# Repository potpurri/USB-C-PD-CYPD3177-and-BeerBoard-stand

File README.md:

# USB Power Delivery Board (CYPD-3177) / BeerBoard-stand

**THIS IS AN OLD DESIGN, FOR VER 2 LOOK AT [THIS REPOSITORY](https://github.com/potpurri/USB-C_PD_Board_V2_CYPD3177).**

This **USB Power Delivery (PD) Board** is based around the **CYPD-3177** chipset. The board allows users to select the desired output **voltage** and **current** using onboard switches, making it ideal for powering my **breadboard projects**. [Schematic can be found here.](https://github.com/potpurri/USB-C-PD-CYPD3177-and-BeerBoard-stand/blob/f3c342192d2ab72d846928ec36ac7f8050d37a6a/imgs/Schematic.pdf)

Users can choose between the following **voltage levels**: **5V, 9V, 12V, 15V, and 20V**, and **current levels**: **1A, 2A, 3A, 4A, and 5A**, depending on the configuration and power supply capabilities.

(The underside of the board also functions as a stand for the [BeerBoard](https://github.com/potpurri/BeerBoard))

The board is soldered by me using a [Pinecil V2](https://wiki.pine64.org/wiki/Pinecil) by PINE64  and [MHP50](https://e-design.com.cn/en/Mini-Hot-Plate-Preheater-MHP50-PG9555615) by MiniWare.

## Key Features
- Based on the **CYPD-3177** USB PD controller
- User-selectable output **voltage**: **5V, 9V, 12V, 15V, and 20V**
- User-selectable output **current**: **1A, 2A, 3A, 4A, and 5A**
- Supports standard USB Power Delivery profiles for flexible power output; compact and versatile

## Images

### Assembled Images

### 3D Image

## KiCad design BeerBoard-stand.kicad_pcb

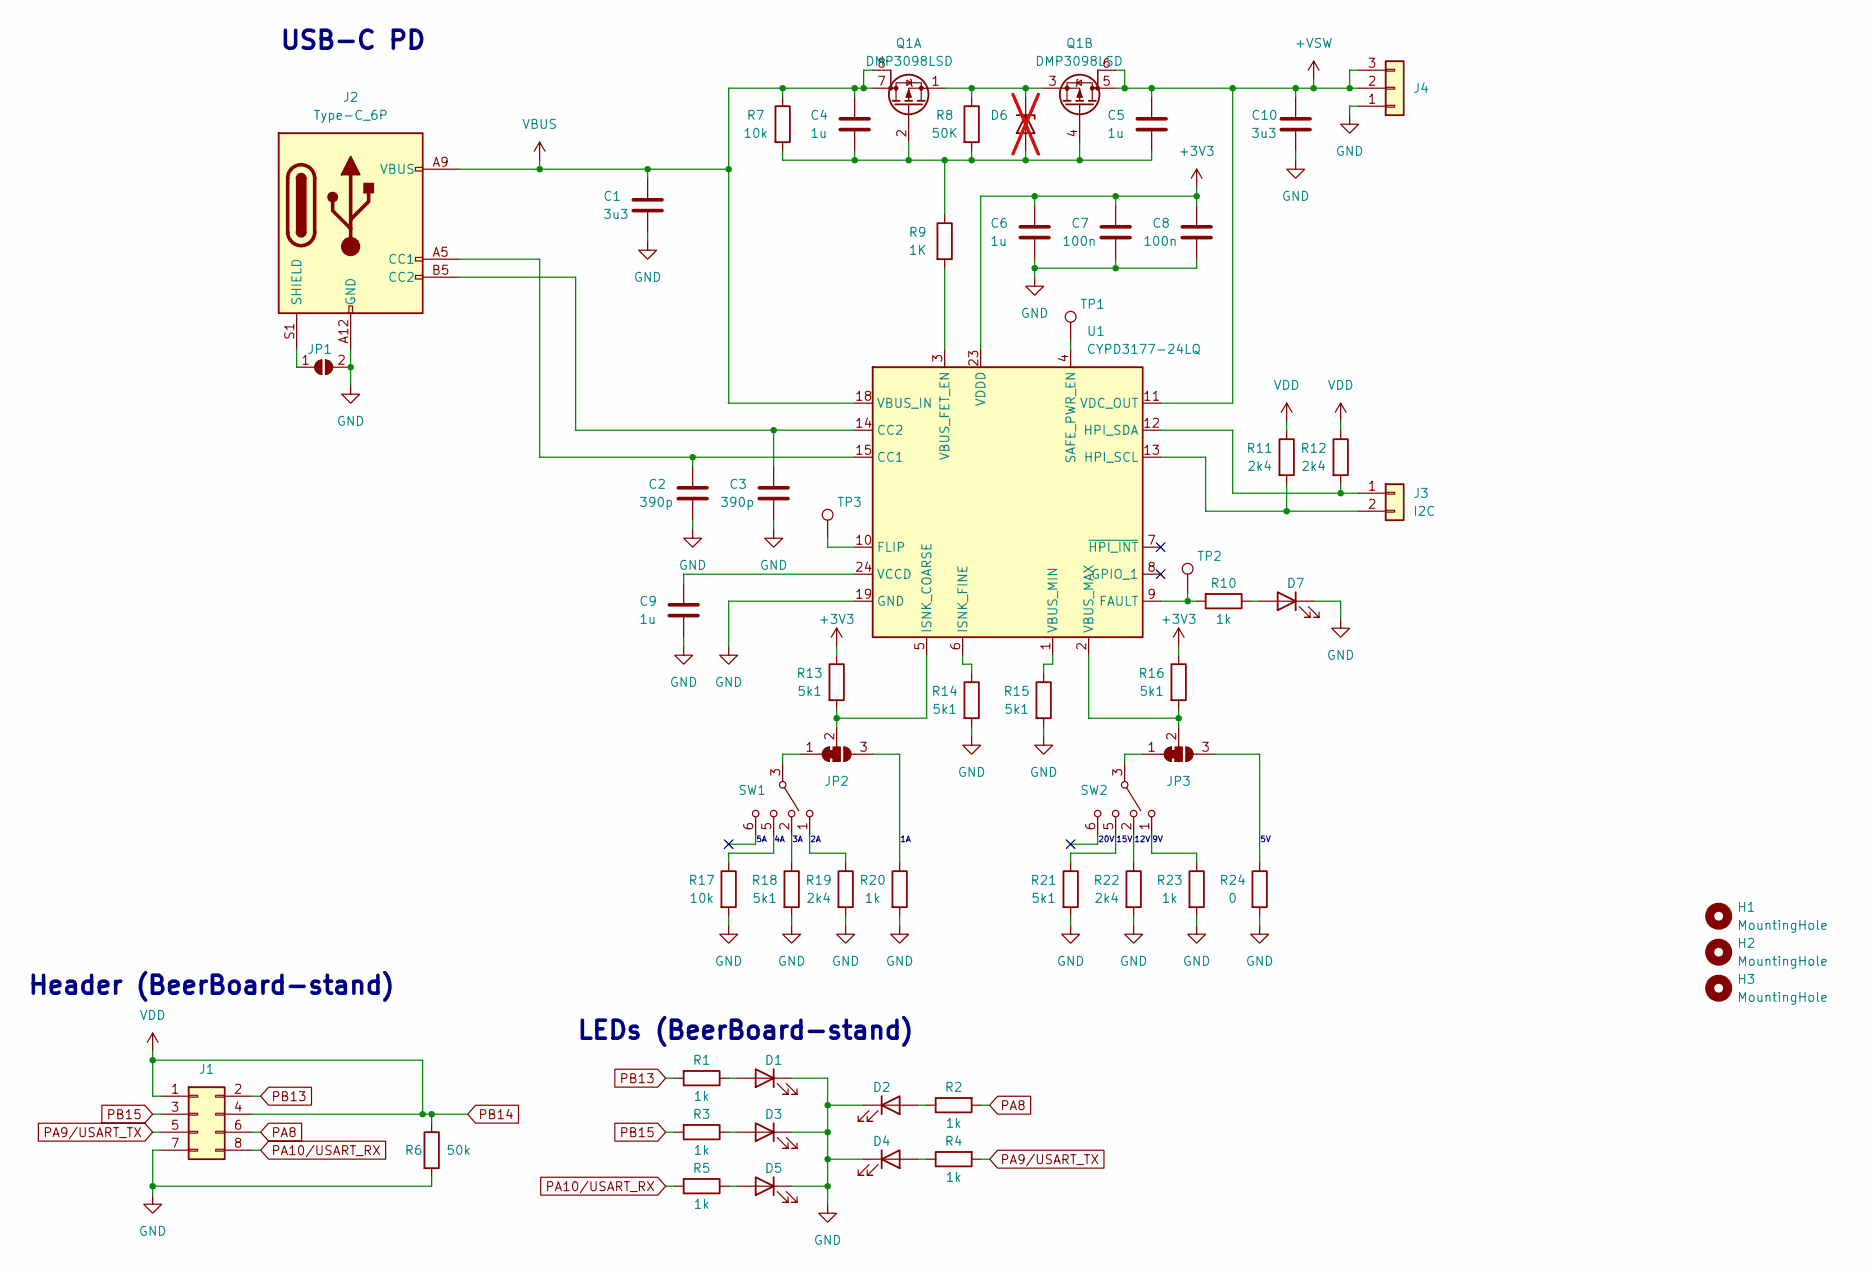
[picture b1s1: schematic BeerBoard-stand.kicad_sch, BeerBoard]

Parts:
C1, C10: 3u3; C_0805_2012Metric_Pad1.18x1.45mm_HandSolder
C2, C3: 390p; C_0603_1608Metric_Pad1.08x0.95mm_HandSolder
C4, C5, C6, C9: 1u; C_0805_2012Metric_Pad1.18x1.45mm_HandSolder
C7, C8: 100n; C_0603_1608Metric_Pad1.08x0.95mm_HandSolder
D1, D2, D3, D4, D5, D7: LED; LED_0805_2012Metric_Pad1.15x1.40mm_HandSolder
D6: D_Zener; D_DO-35_SOD27_P7.62mm_Horizontal; not fitted
H1, H2, H3: MountingHole; MountingHole_3.2mm_M3
J1: Conn_02x04_Odd_Even; PinHeader_2x04_P2.54mm_Vertical
J2: Type-C_6P; USB_C_Receptacle_GCT_USB4125-xx-x-0190_6P_TopMnt_Horizontal
J3: I2C; PinHeader_1x02_P2.54mm_Vertical
J4: Conn_01x03; PinHeader_1x03_P2.54mm_Vertical
JP1: SolderJumper_2_Open; SolderJumper-2_P1.3mm_Open_RoundedPad1.0x1.5mm
JP2, JP3: SolderJumper_3_Bridged12; SolderJumper-3_P1.3mm_Bridged2Bar12_RoundedPad1.0x1.5mm_Num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
Q1: DMP3098LSD; SOIC-8-1EP_3.9x4.9mm_P1.27mm_EP2.29x3mm
R1, R2, R3, R4, R5, R10, R20, R23: 1k; R_0603_1608Metric
R6: 50k; R_0603_1608Metric
R7, R17: 10k; R_0603_1608Metric
R8: 50K; R_0603_1608Metric
R9: 1K; R_0603_1608Metric
R11, R12, R19, R22: 2k4; R_0603_1608Metric
R13, R14, R15, R16, R18, R21: 5k1; R_0603_1608Metric
R24: 0; R_0603_1608Metric
SW1, SW2: SK-14D01-G 6
TP1, TP2, TP3: TestPoint; TestPoint_Pad_1.0x1.0mm
U1: CYPD3177-24LQ; QFN-24-1EP_4x4mm_P0.5mm_EP2.75x2.75mm

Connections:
+3V3: C6.1, C7.1, C8.1, R13.1, R16.1, U1.23 (VDDD)
+VSW: C5.1, C10.1, J4.2, J4.3, Q1.5 (D), Q1.6 (G), U1.11 (VDC_OUT)
CC1: C2.1, J2.A5 (CC1), U1.15 (CC1)
CC2: C3.1, J2.B5 (CC2), U1.14 (CC2)
GND: C1.2, C2.2, C3.2, C6.2, C7.2, C8.2, C9.2, C10.2, D1.1 (K), D2.1 (K), D3.1 (K), D4.1 (K), D5.1 (K), D7.1 (K), J1.7, J2.A12 (GND), J2.B12 (GND), J4.1, JP1.2 (B), R6.2, R14.2, R15.2, R17.2, R18.2, R19.2, R20.2, R21.2, R22.2, R23.2, R24.2, U1.19 (GND), U1.22 (GND), U1.25 (GND)
unnamed: D1.2 (A), R1.1
unnamed: D2.2 (A), R2.1
unnamed: D3.2 (A), R3.1
unnamed: D4.2 (A), R4.1
unnamed: D5.2 (A), R5.1
unnamed: C4.2, C5.2, D6.2 (A), Q1.2 (G), Q1.4 (G), R7.2, R8.2, R9.1
unnamed: D6.1 (K), Q1.1 (S), Q1.3 (S), R8.1
unnamed: D7.2 (A), R10.1
unnamed: J2.S1 (SHIELD), JP1.1 (A)
unnamed: J3.1, R12.2, U1.12 (HPI_SDA)
unnamed: J3.2, R11.2, U1.13 (HPI_SCL)
unnamed: JP2.1 (A), SW1.3, SW1.4
unnamed: JP2.3 (B), R20.1
unnamed: JP2.2 (C), R13.2, U1.5 (ISNK_COARSE)
unnamed: JP3.1 (A), SW2.3, SW2.4
unnamed: JP3.3 (B), R24.1
unnamed: JP3.2 (C), R16.2, U1.2 (VBUS_MAX)
unnamed: R17.1, SW1.5
unnamed: R18.1, SW1.2
unnamed: R19.1, SW1.1
unnamed: R21.1, SW2.5
unnamed: R22.1, SW2.2
unnamed: R23.1, SW2.1
unnamed: R10.2, TP2.1, U1.9 (FAULT)
unnamed: TP3.1, U1.10 (FLIP)
unnamed: R14.1, U1.6 (ISNK_FINE)
unnamed: TP1.1, U1.4 (SAFE_PWR_EN)
unnamed: R9.2, U1.3 (VBUS_FET_EN)
unnamed: R15.1, U1.1 (VBUS_MIN)
unnamed: C9.1, U1.24 (VCCD)
PA8: J1.6, R2.2
PA9/USART_TX: J1.5, R4.2
PA10/USART_RX: J1.8, R5.2
PB13: J1.2, R1.2
PB14: J1.1, J1.4, R6.1, R11.1, R12.1
PB15: J1.3, R3.2
VBUS: C1.1, C4.1, J2.A9 (VBUS), J2.B9 (VBUS), Q1.7 (D), Q1.8 (G), R7.1, U1.18 (VBUS_IN)

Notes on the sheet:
USB-C PD
Header (BeerBoard-stand)
15V
12V
LEDs (BeerBoard-stand)
20V

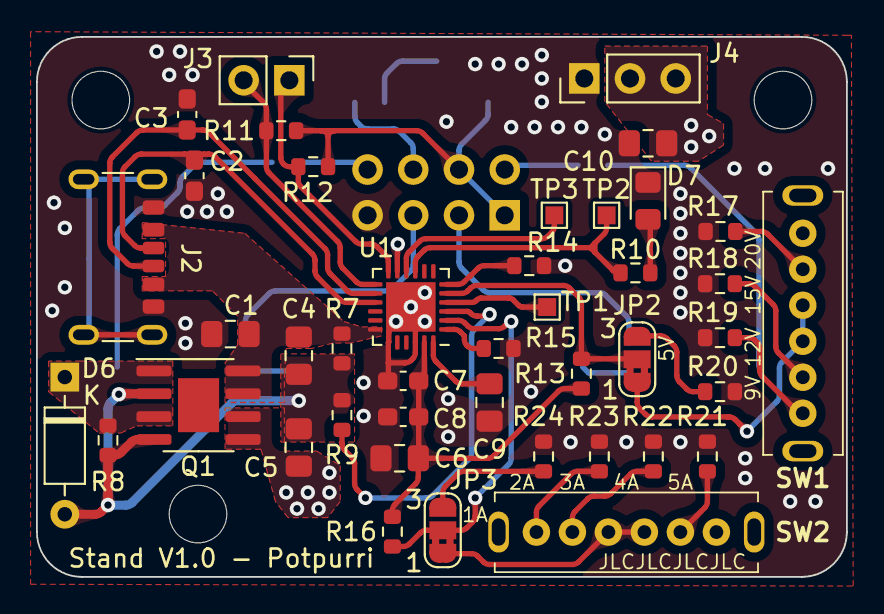
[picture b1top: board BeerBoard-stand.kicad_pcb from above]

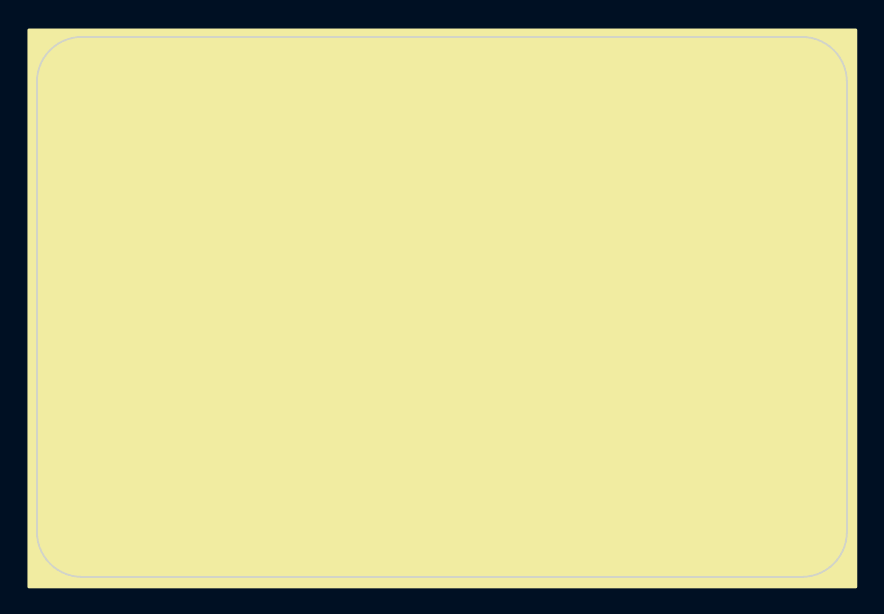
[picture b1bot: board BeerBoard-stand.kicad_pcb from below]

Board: 4 copper layers, 45.0 x 30.0 mm, 58 parts (13 on the bottom side), 42 nets.

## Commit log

2024-09-08 Some updates, added images
2024-09-08 readme fix
